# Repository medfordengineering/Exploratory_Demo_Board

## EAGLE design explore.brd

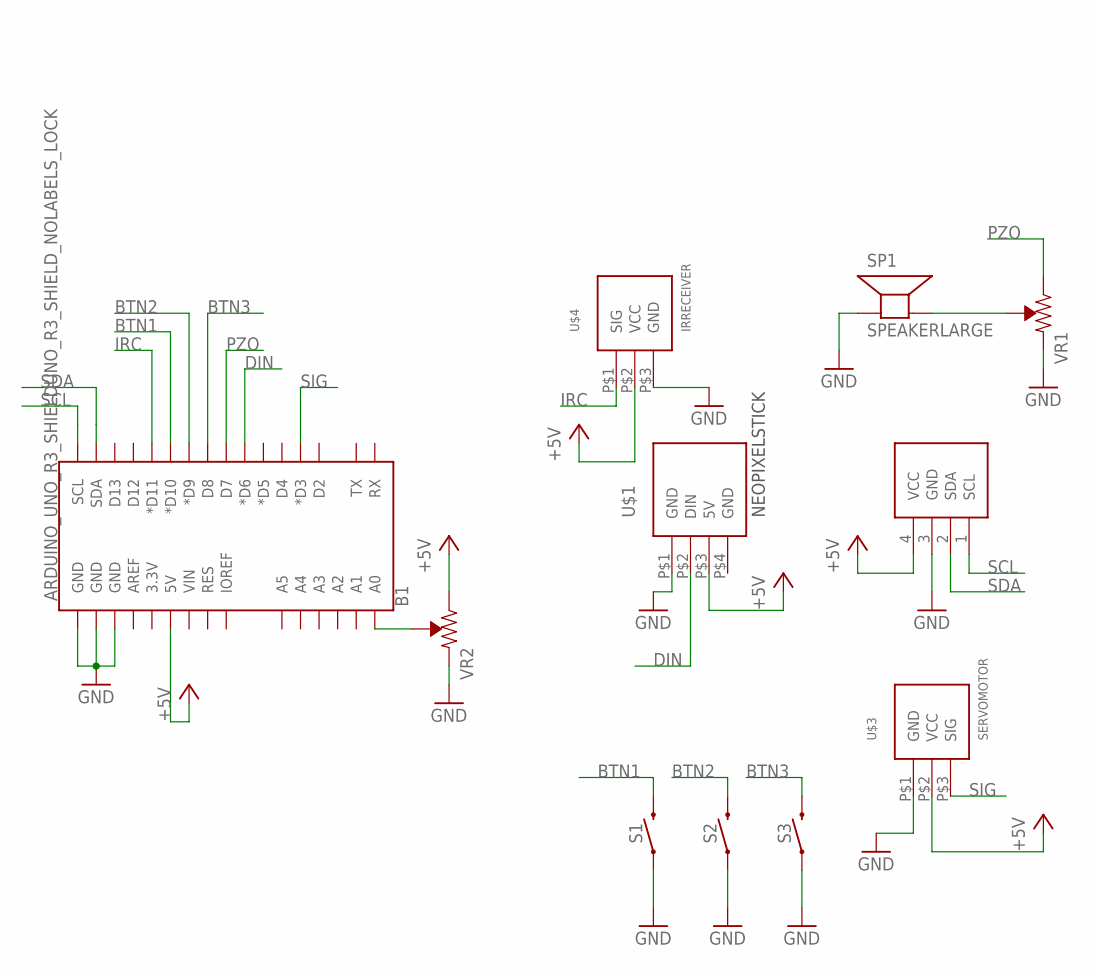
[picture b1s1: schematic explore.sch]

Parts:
B1: ARDUINO_UNO_R3_SHIELDUNO_R3_SHIELD_NOLABELS_LOCK; UNO_R3_SHIELD_NOLABELS_LOCK
S1, S2, S3: MOMENTARY-SWITCH-SPST-PTH-6.0MM; TACTILE_SWITCH_PTH_6.0MM
SP1: SPEAKERLARGE; 2-HOLE_LARGE
U$1: NEOPIXELSTICK
U$2: 4DIGITDISPLAYOUTLINE; 4DIGITDISPLAY
U$3: SERVOMOTOR; 3-HOLE-LARGE
U$4: IRRECEIVER; 3-HOLE-LARGE
VR1, VR2: TRIMPOTSTANDARD; POTENTIOMETER

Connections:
+5V: B1.5V, U$1.P$3 (5V), U$2.4 (VCC), U$3.P$2 (VCC), U$4.P$2 (VCC), VR2.P$3 (CW)
BTN1: B1.D10 (*D10), S1.3 (2)
BTN2: B1.D9 (*D9), S2.3 (2)
BTN3: B1.D8, S3.3 (2)
DIN: B1.D6 (*D6), U$1.P$2 (DIN)
GND: B1.GND@0 (GND), B1.GND@1 (GND), B1.GND@2 (GND), S1.1, S2.1, S3.1, SP1.P$1 (+), U$1.P$1 (GND), U$2.3 (GND), U$3.P$1 (GND), U$4.P$3 (GND), VR1.P$1 (CCW), VR2.P$1 (CCW)
IRC: B1.D11 (*D11), U$4.P$1 (SIG)
unnamed: B1.A0, VR2.P$2 (WIPER)
unnamed: SP1.P$2 (-), VR1.P$2 (WIPER)
PZO: B1.D7, VR1.P$3 (CW)
SCL: B1.SCL, U$2.1 (SCL)
SDA: B1.SDA, U$2.2 (SDA)
SIG: B1.D3 (*D3), U$3.P$3 (SIG)

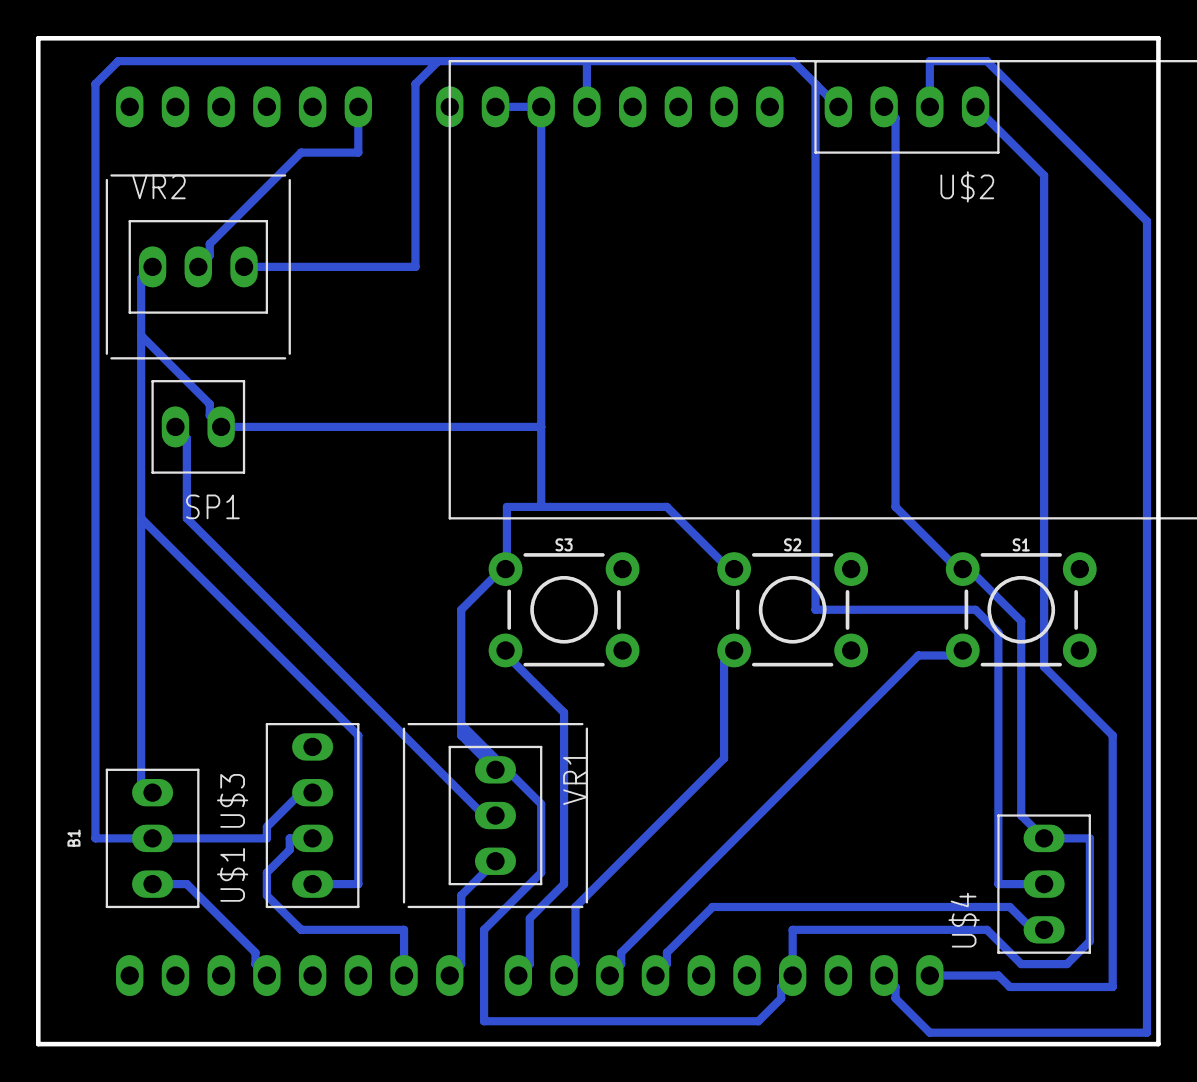
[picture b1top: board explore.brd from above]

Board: 2 copper layers, 62.2 x 55.9 mm, 11 parts (0 on the bottom side), 13 nets.

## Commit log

2018-07-13 added all components
2018-07-13 finihed and checked first draft
2018-07-13 refinements
2018-08-23 Working Version of Board

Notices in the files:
parts and their libraries:
SparkFun-Switches: Licensing: Creative Commons ShareAlike 4.0 International - https://creativecommons.org/licenses/by-sa/4.0
